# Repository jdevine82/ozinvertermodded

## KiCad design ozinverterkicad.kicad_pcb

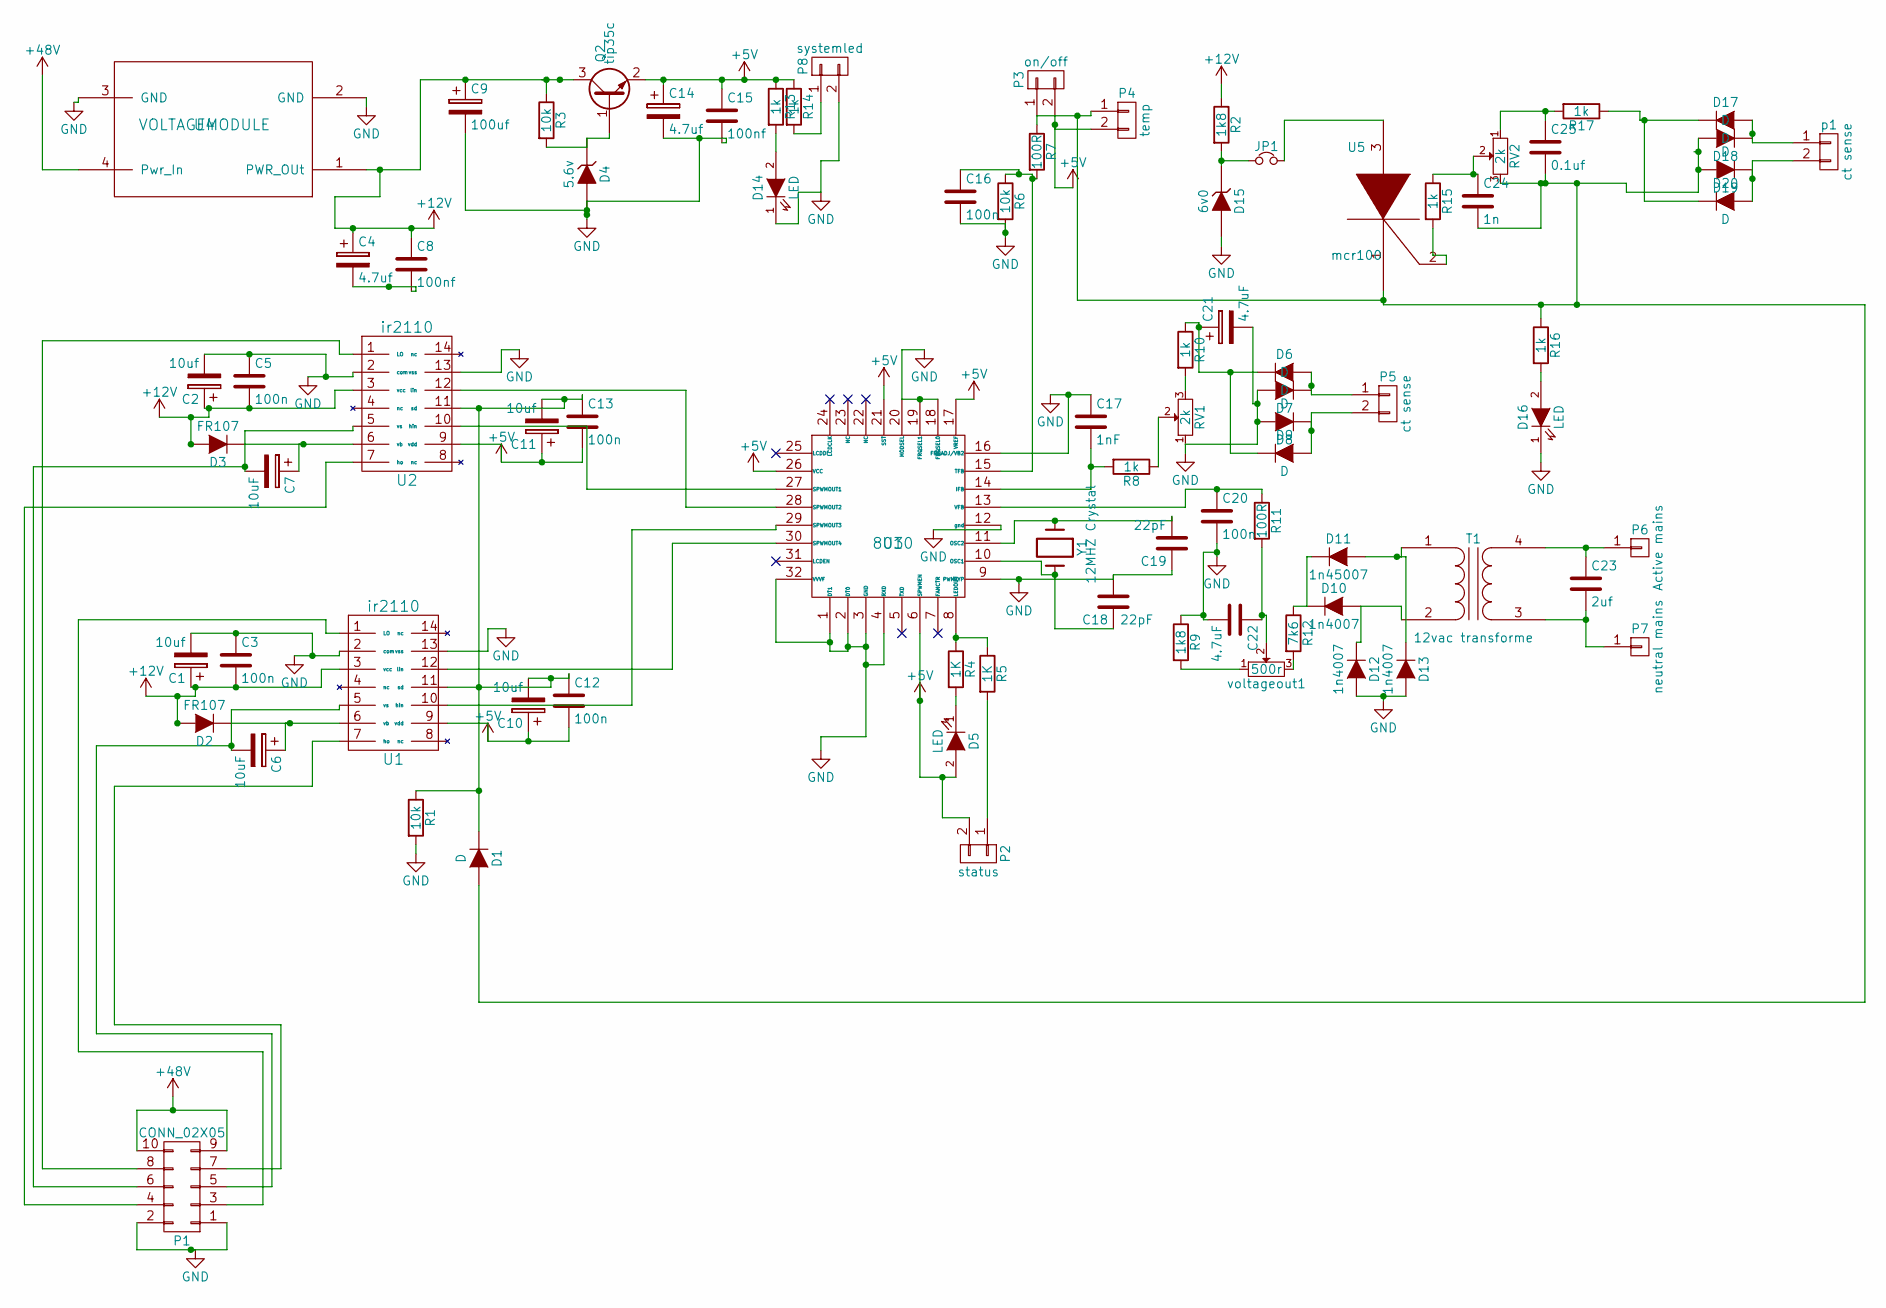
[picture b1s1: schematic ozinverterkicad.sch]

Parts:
C1, C2: 10uf; C_Radial_D5_L6_P2.5
C3, C5, C12, C13, C16, C20: 100n; C_Rect_L7_W2.5_P5
C4, C14: 4.7uf; C_Radial_D5_L6_P2.5
C6, C7: 10uF; C_Radial_D5_L6_P2.5
C8, C15: 100nf; C_Rect_L7_W2.5_P5
C9: 100uf; C_Radial_D6.3_L11.2_P2.5
C10, C11: 10uf; C_Radial_D5_L11_P2.5
C17: 1nF; C_Rect_L7_W2.5_P5
C18, C19: 22pF; C_Disc_D3_P2.5
C21, C22: 4.7uF; C_Radial_D5_L6_P2.5
C23: 2uf; C_Rect_L27_W11_P22
C24: 1n; C_Disc_D3_P2.5
C25: 0.1uf; C_Radial_D5_L6_P2.5
D1, D6, D7, D8, D9, D17, D18, D19, D20: D; Diode_DO-41_SOD81_Vertical_AnodeUp
D2, D3: FR107; Diode_DO-41_SOD81_Vertical_AnodeUp
D4: 5.6v; Diode_DO-41_SOD81_Vertical_AnodeUp
D5, D14, D16: LED; LED-5MM
D10, D12, D13: 1n4007; Diode_DO-41_SOD81_Vertical_AnodeUp
D11: 1n45007; Diode_DO-41_SOD81_Vertical_AnodeUp
D15: 6v0; Diode_DO-41_SOD81_Vertical_AnodeUp
JP1: reset; Molex_KK-6410-02_02x2.54mm_Straight
P1: CONN_02X05; IDC_Header_Straight_10pins
P2: status; Molex_KK-6410-02_02x2.54mm_Straight
P3: on/off; Molex_KK-6410-02_02x2.54mm_Straight
P4: temp; Molex_KK-6410-02_02x2.54mm_Straight
P5: ct sense; Molex_KK-6410-02_02x2.54mm_Straight
P6: Active mains; 1pin
P7: neutral mains; 1pin
P8: systemled; Molex_KK-6410-02_02x2.54mm_Straight
Q2: tip35c; TO-247_Vertical_Neutral123
R1, R3, R6: 10k; Resistor_Horizontal_RM7mm
R2, R9: 1k8; Resistor_Horizontal_RM7mm
R4, R5: 1K; Resistor_Horizontal_RM7mm
R7, R11: 100R; Resistor_Horizontal_RM7mm
R8, R10, R13, R14, R15, R16, R17: 1k; Resistor_Horizontal_RM7mm
R12: 7k6; Resistor_Horizontal_RM7mm
RV1, RV2: 2k; RV2X4
T1: 12vac transforme; 3wtransformer
U1, U2: ir2110; DIP-14_W7.62mm
U3: 8010; DIP-32_W15.24mm
U4: VOLTAGEMODULE; lm2596hvsmodule
U5: mcr100; TO-92_Molded_Narrow
Y1: 12MHZ Crystal; Crystal_HC49-U_Vertical
p1: ct sense; Molex_KK-6410-02_02x2.54mm_Straight
voltageout1: 500r; RV2X4

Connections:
+5V: C10.1, C11.1, C12.2, C13.2, C14.1, C15.1, D5.2 (A), P2.2, P3.2, P4.2, Q2.2 (E), R13.1, R14.1, U1.9 (vdd), U2.9 (vdd), U3.6 (SPWMEN), U3.17 (VREF), U3.21 (SST), U3.26 (VCC)
+12V: C1.1, C2.1, C3.2, C4.1, C5.2, C8.1, C9.1, D2.2 (A), D3.2 (A), Q2.3 (C), R2.1, R3.1, U1.3 (vcc), U2.3 (vcc), U4.1 (PWR_OUt)
+48V: P1.9, P1.10, U4.4 (Pwr_In)
GND: C1.2, C2.2, C3.1, C5.1, C9.2, C14.2, C15.2, C16.2, C17.1, C18.2, C19.1, C20.2, C21.2, C22.2, D4.2 (A), D7.2 (A), D8.2 (A), D12.2 (A), D13.2 (A), D14.1 (K), D15.2 (A), D16.1 (K), P1.1, P1.2, P8.2, R1.2, R6.2, R9.1, RV1.1, U1.2 (com), U1.13 (vss), U2.2 (com), U2.13 (vss), U3.1 (DT1), U3.2 (DT0), U3.3 (GND), U3.4 (RXD), U3.9 (PWMTYP), U3.12 (gnd), U3.16 (FRQADJ/VB2), U3.18 (FRQSEL0), U3.19 (FRQSEL1), U3.20 (MODSEL), U3.32 (VVVF), U4.2 (GND), U4.3 (GND); also elsewhere on the board
unnamed: C4.2, C8.2
unnamed: C6.1, D2.1 (K), U1.6 (vb)
unnamed: C6.2, P1.5, U1.5 (vs)
unnamed: C7.1, D3.1 (K), U2.6 (vb)
unnamed: C7.2, P1.6, U2.5 (vs)
unnamed: C10.2, C11.2, C12.1, C13.1, D1.1 (K), R1.1, U1.11 (sd), U2.11 (sd)
unnamed: C16.1, R6.1, R7.2, U3.15 (TFB)
unnamed: C17.2, R8.2, U3.14 (IFB)
unnamed: C18.1, U3.10 (OSC1), Y1.2
unnamed: C19.2, U3.11 (OSC2), Y1.1
unnamed: C20.1, R11.1, U3.13 (VFB)
unnamed: C21.1, D6.1 (K), D9.1 (K), R10.1
unnamed: C22.1, R11.2, voltageout1.2
unnamed: C23.1, P6.1, T1.4 (SB)
unnamed: C23.2, P7.1, T1.3 (SA)
unnamed 19: C24.1, R15.1, RV2.2; also elsewhere on the board
unnamed 20: C24.2, C25.2, D1.2 (A), D18.2 (A), D19.2 (A), P3.1, P4.1, R7.1, R16.1, RV2.3, U5.1 (K); also elsewhere on the board
unnamed 21: C25.1, R17.2, RV2.1; also elsewhere on the board
unnamed: D4.1 (K), Q2.1 (B), R3.2
unnamed: D5.1 (K), R4.2
unnamed: D6.2 (A), D7.1 (K), P5.1
unnamed: D8.1 (K), D9.2 (A), P5.2
unnamed: D10.1 (K), D11.1 (K), R12.1
unnamed: D10.2 (A), D12.1 (K), T1.2 (AB)
unnamed: D11.2 (A), D13.1 (K), T1.1 (AA)
unnamed: D14.2 (A), R13.2
unnamed: D15.1 (K), JP1.1, R2.2
unnamed: D16.2 (A), R16.2
unnamed: D17.1 (K), D20.1 (K), R17.1
unnamed: D17.2 (A), D18.1 (K), p1.1
unnamed: D19.1 (K), D20.2 (A), p1.2
unnamed: JP1.2, U5.3 (A)
unnamed: P1.3, U1.1 (LO)
unnamed: P1.4, U2.7 (ho)
unnamed: P1.7, U1.7 (ho)
unnamed: P1.8, U2.1 (LO)
unnamed: P2.1, R5.2
unnamed: P8.1, R14.2
unnamed: R4.1, R5.1, U3.8 (LEDOUT)
unnamed 43: R8.1, RV1.2; also elsewhere on the board
unnamed: R9.2, voltageout1.1
unnamed 45: R10.2, RV1.3; also elsewhere on the board
unnamed: R12.2, voltageout1.3
unnamed: R15.2, U5.2 (G)
unnamed: U1.10 (hin), U3.29 (SPWMOUT3)
unnamed: U1.12 (lin), U3.30 (SPWMOUT4)
unnamed: U2.10 (hin), U3.27 (SPWMOUT1)
unnamed: U2.12 (lin), U3.28 (SPWMOUT2)

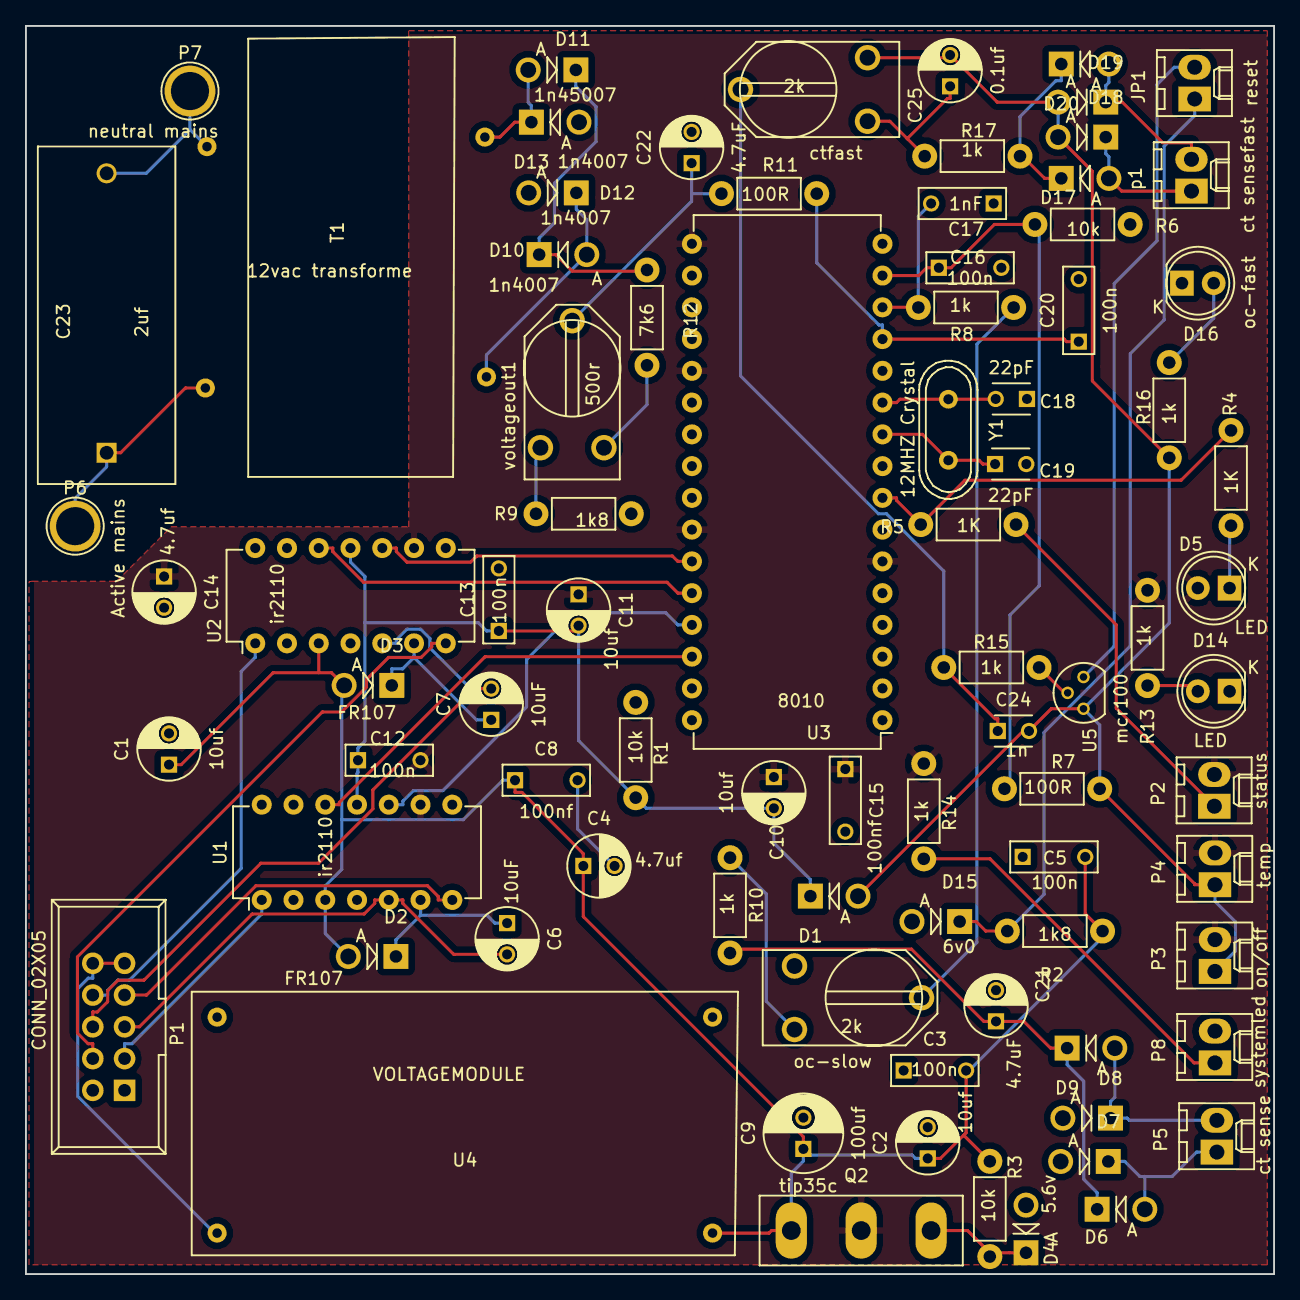
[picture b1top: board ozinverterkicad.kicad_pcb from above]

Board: 2 copper layers, 99.8 x 99.8 mm, 83 parts (0 on the bottom side), 52 nets.

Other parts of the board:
ctfast: 2k; RV2X4
oc-slow: 2k; RV2X4

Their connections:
GND: oc-slow.1; also elsewhere on the board
unnamed 19: ctfast.2; also elsewhere on the board
unnamed 20: ctfast.3; also elsewhere on the board
unnamed 21: ctfast.1; also elsewhere on the board
unnamed 43: oc-slow.2; also elsewhere on the board
unnamed 45: oc-slow.3; also elsewhere on the board

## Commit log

2016-09-04 changed about.txt
2016-09-04 added schematic in pdf
2016-10-15 added extra ct sense
2016-10-15 added extra ct routed
2016-10-15 added pdf
2016-10-15 changedboard outline to under 100x100
2017-08-08 changed plug around for correct pinout
